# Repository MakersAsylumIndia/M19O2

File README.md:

# M19O2
DiY Oxygen Concentrator based on / inspired by the [OpenOx](https://github.com/hacklabkyiv/openox), [Marut](https://www.technido.com/marut), [RepRap](https://github.com/RepRapLtd/Oxygen-concentrator) and [Project Apollo](https://github.com/oxycon/ProjectApollo) platforms.

## About

Read about the project on [Hackaday](https://hackaday.com/2021/04/26/indian-makers-respond-to-the-covid-19-pandemic-by-producing-oxygen-concentrators/).
Also check out the project on the [hackaday.io](https://hackaday.io/project/181201-m19o2-oxygen-concentrator) project page.

The **M19O2** Oxygen Concentrator is "Open Source Hardware" as certified by the [OSHWA](https://certification.oshwa.org/in000029.html).
OSHWA UID for the M19O2 is **IN000029**

<a href="https://certification.oshwa.org/in000029.html">

## Contribute

You can contribute on the [Ketto fundraiser page](https://www.ketto.org/fundraiser/m19-oxygen-concentrators-make-in-india)

## Coordination lists

- [Notion workspace](https://www.notion.so/M-19-Collective-b44b9d8d7dd14d5d86d417facf0f4141) for the M19 collective.
- [M19O2 Master](https://docs.google.com/spreadsheets/d/1rJZ5P0rF2Or8yu0H8HEPz25RP8kTAXxbNVU87DqD-eM/edit#gid=0) sheet tracks the city-wise coordinators, tools, FAQs etc.
- [BOM M19O2](https://docs.google.com/spreadsheets/d/1gmmdXTP3EQk-4hCGVYj-FxzUMADlT8mw354VPmYt5A4/edit#gid=870920932) sheet lists the master Bill of Materials (BOM) along with city-wise BOM
- [Starting a community lab](https://docs.google.com/document/d/1oR9rhGmbcnoSBjzQCYwE9Anocvr0q5_VmuVkbnycx18/edit?usp=sharing) document and [Build List for Labs](https://docs.google.com/spreadsheets/d/1DynT9Mh8jcV9qHxwFuQxj1fcQQHj_v_ymwpoZD1L23g/edit?usp=sharing) sheet for lab onboarding information and coordination.

## Engineering

- [Labview testbench](engineering/software/M19-oxygen-concentrator-testbench) is a testbench executable developed by [Fracktal Works](https://github.com/FracktalWorks), useful for tuning the performance of your concentrator prototypes.
- [Computer-aided Design/Engineering](engineering/cad-cae) for design, version control and simulation data related to the M19O2 and its iterations. Committed to open-source and open-innovation.
- [Electronics](engineering/electronics) for all things electronics, including comprehensive design and development data of DIY [Oxygen Analyzers](engineering/electronics/oxygen_analysers) and other [subprojects](engineering/electronics/subprojects).

## How to use this repo

Open a terminal on your computer. Run

```bash
git clone https://github.com/MakersAsylumIndia/M19O2 && cd M19O2
git submodule update --init --recursive
```
The repository shall be available on your computer.
To periodically update the contents,

```bash
cd M19O2
git pull
git submodule update --init --recursive
```

## How to contribute to this repository

Fork this repository. You can find the command for this on the top-right of the webpage. This shall create a personal, updateable copy of this repository on your github account.

On your computer terminal, run

```bash
git clone https://github.com/<your-username>/M19O2 && cd M19O2
git submodule update --init --recursive
```
Add your contributions to this repository and save on github.

```bash
cd M19O2
git add .
git commit -m "<your-commit-message>"
git push origin
```

To contribute your work to the M19 Collective, open your repository in a browser and issue a pull request from your repository to the one at [Makers' Asylum](https://github.com/MakersAsylumIndia).

## License

Licenses

#### Hardware
CERN Open Hardware License Version 2 - Strongly Reciprocal ([CERN-OHL-S-2.0](https://spdx.org/licenses/CERN-OHL-S-2.0.html)).

#### Software
MIT open source [license](http://opensource.org/licenses/MIT).

#### Documentation:
<br />This work is licensed under a <a rel="license" href="http://creativecommons.org/licenses/by/4.0/">Creative Commons Attribution 4.0 International License</a>.

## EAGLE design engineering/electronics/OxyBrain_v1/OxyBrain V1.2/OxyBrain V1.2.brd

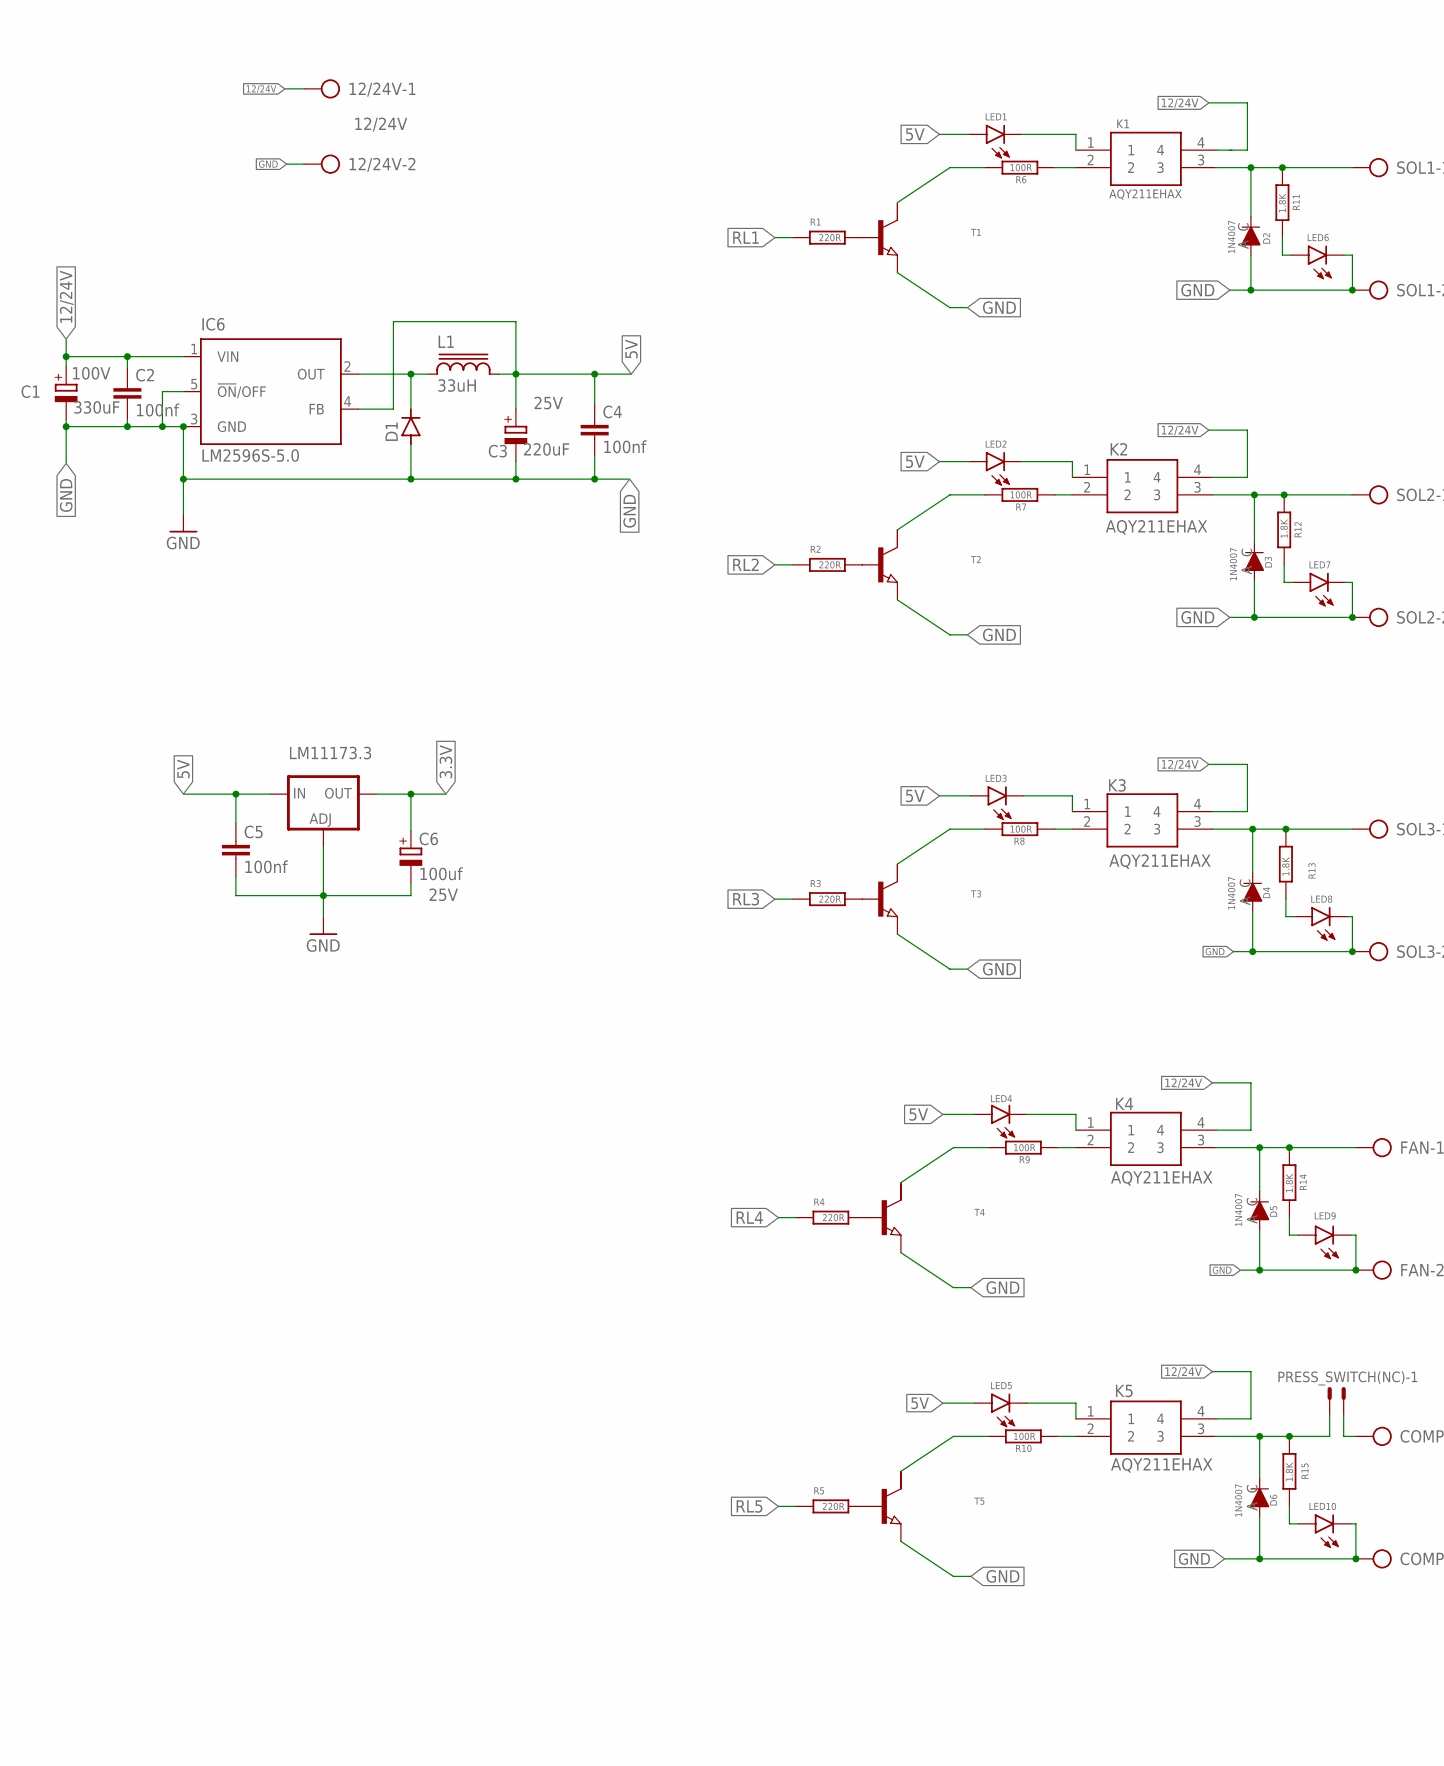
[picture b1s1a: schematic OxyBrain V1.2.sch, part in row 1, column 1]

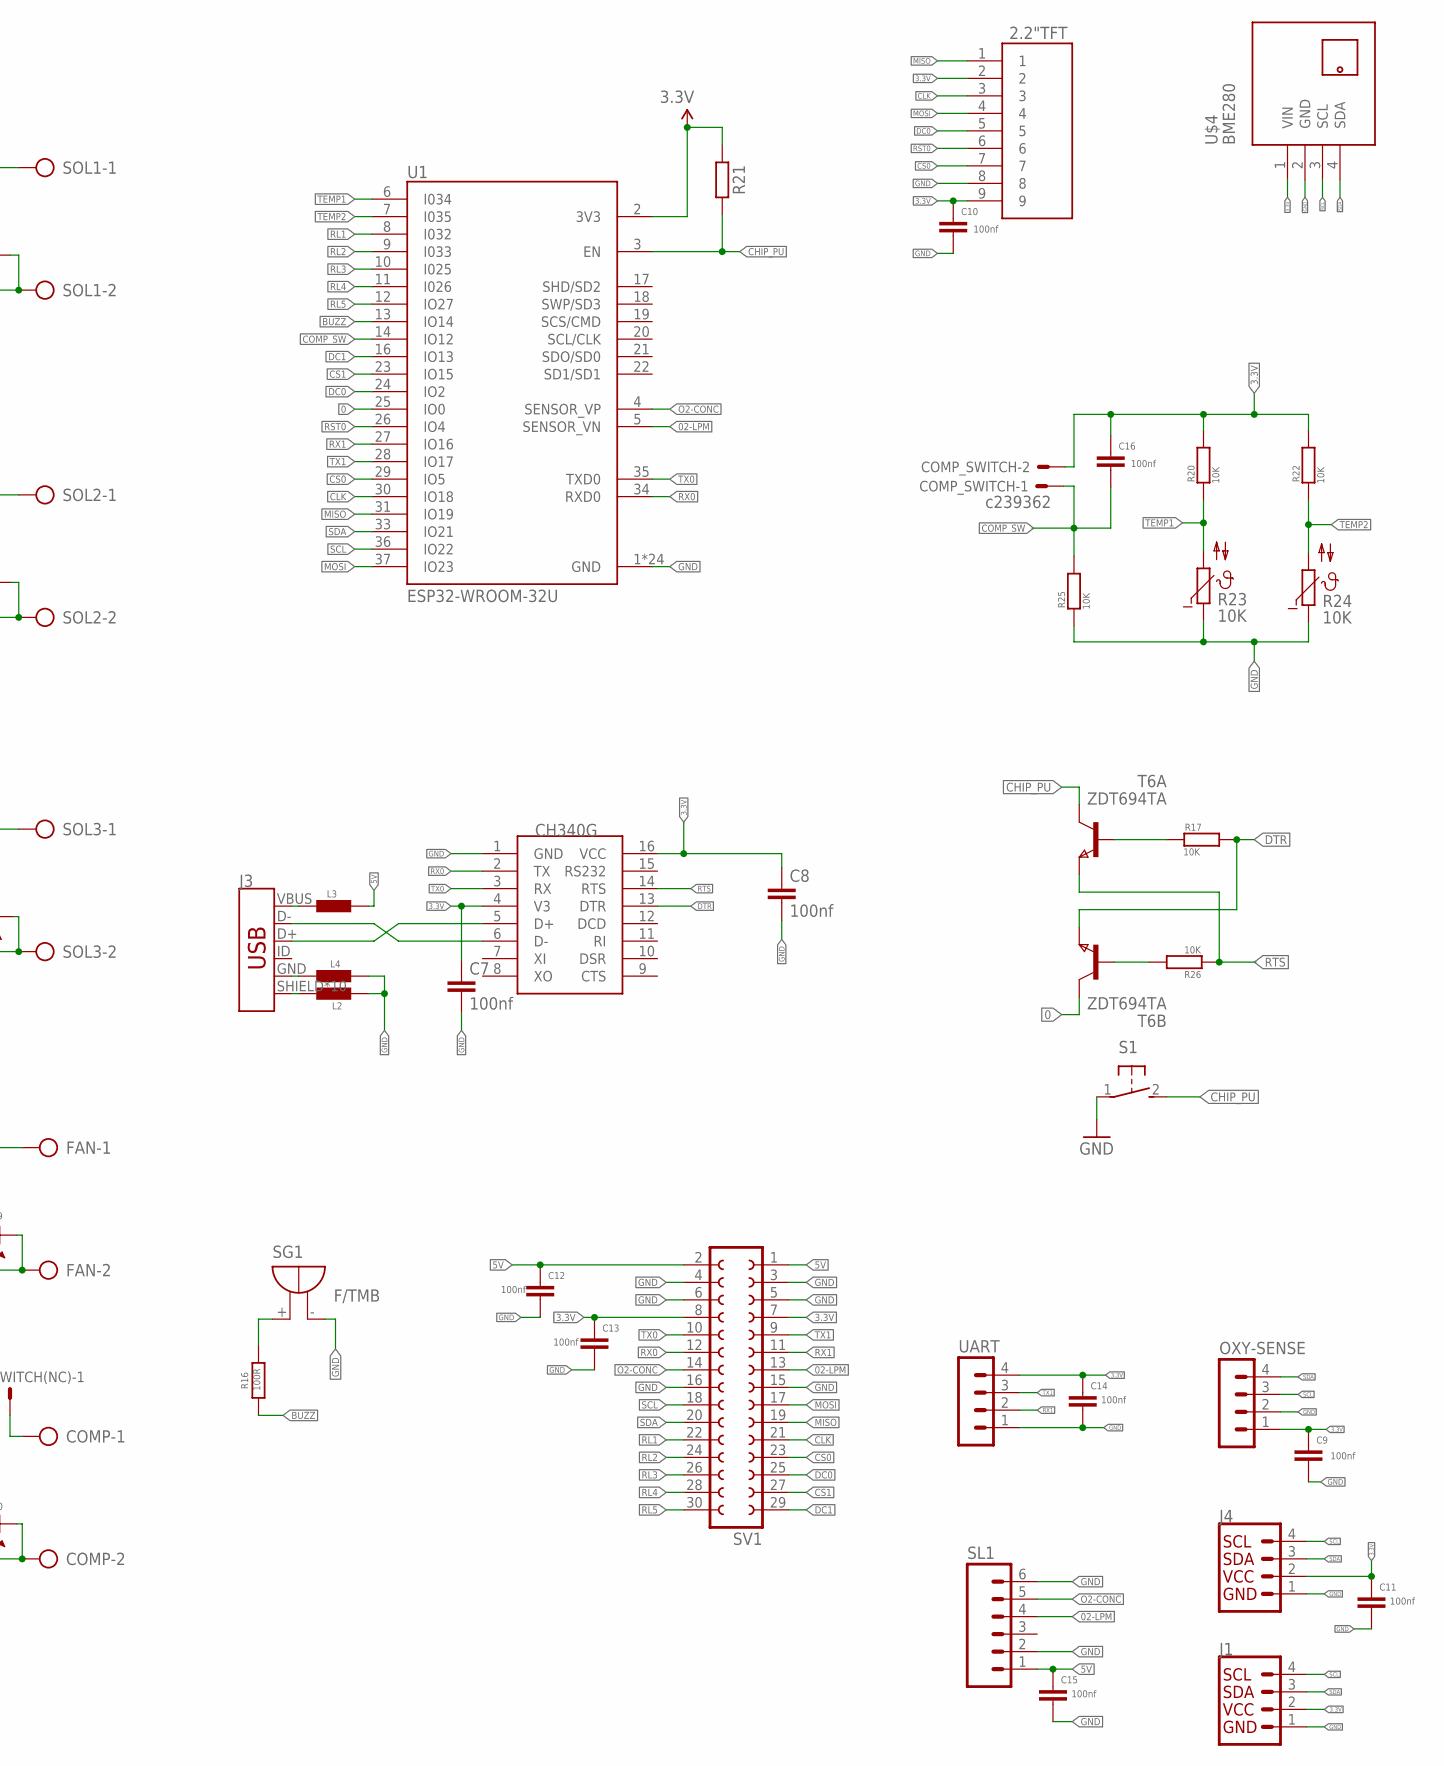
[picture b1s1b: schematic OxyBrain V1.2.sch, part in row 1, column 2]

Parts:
2.2"TFT: 1735446-9; SHDR9W60P0X200_1X9_2000X520X63
12/24V: 12/24V; AK500/2
C1: 330uF; 140CLH-1010; VOLTAGE 100V
C2, C4, C5, C7, C8, C9, C10, C11, C12, C13, C14, C15, C16: 100nf; C1206
C3: 220uF; 153CLV-0605; VOLTAGE 25V
C6: 100uf; 153CLV-0605; VOLTAGE 25V
COMP: AK500/2
COMP_SWITCH: c239362; 22-23-2021
D1: DIODE-SOD123; SOD123
D2, D3, D4, D5, D6: 1N4007; SOD-123FL
FAN: AK500/2
IC6: LM2596S-5.0; TO263-5
J1, J4: I2C_STANDARD; 1X04
J3: USB_MICRO-B_HALF_PTH_MILL; USB-MICROB-PTH-MILL
K1, K2, K3, K4, K5: AQY211EHAX; AQY21(SMD_DIP)
L1: 33uH; CDRH127/LD
L2, L3, L4: BLM15HD102SN1; 0402
LED1, LED2, LED3, LED4, LED5, LED6, LED7, LED8, LED9, LED10: LEDCHIPLED_1206; CHIPLED_1206
LM11173.3: LD117ADT33TR; DPACK
OXY-SENSE: MA04-1
PRESS_SWITCH(NC): c239362; 22-23-2021
R1, R2, R3, R4, R5: 220R; M1206
R6, R7, R8, R9, R10, R16: 100R; M1206
R11, R12, R13, R14, R15: 1.8K; M1206
R17, R20, R22, R25, R26: 10K; M1206
R21: 10k; M1206
R23, R24: 10K; P640
S1: B3U-1000P(M)-B; DTSM-3
SG1: F/TMB
SL1: M06; 06P
SOL1, SOL2, SOL3: AK500/2
SV1: FE15-2
T1, T2, T3, T4, T5: 600mA/40V; SOT89
T6: ZDT694TA; SM8
U1: ESP32-WROOM-32U; XCVR_ESP32-WROOM-32U
U$1: CH340G; SOIC16
U$4: BME280; TEMP-HUM-PRES-BME280
UART: MA04-1

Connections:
0: T6.7 (C), T6.8 (C), U1.25 (IO0)
02-LPM: SL1.4, SV1.13, U1.5 (SENSOR_VN)
3.3V: 2.2"TFT.2, 2.2"TFT.9, C6.+, C7.1, C8.1, C9.1, C10.1, C11.1, C13.1, C14.1, C16.1, COMP_SWITCH.2, J1.2, J4.2, LM11173.3.4 (OUT), OXY-SENSE.1, R20.1, R21.2, R22.1, SV1.7, SV1.8, U1.2 (3V3), U$1.4 (V3), U$1.16 (VCC), U$4.1 (VIN), UART.4
5V: C3.+, C4.1, C5.1, C12.1, C15.1, IC6.4 (FB), L1.2, L3.2, LED1.A, LED2.A, LED3.A, LED4.A, LED5.A, LM11173.3.3 (IN), SL1.1, SV1.1, SV1.2
12/24V: 12/24V.1, C1.+, C2.1, IC6.1 (VIN), K1.4, K2.4, K3.4, K4.4, K5.4
BUZZ: R16.1, U1.13 (IO14)
CHIP_PU: R21.1, S1.2, T6.5 (C), T6.6 (C), U1.3 (EN)
CLK: 2.2"TFT.3, SV1.21, U1.30 (IO18)
COMP1: COMP.1, PRESS_SWITCH(NC).2
COMP_ON1: D6.C (K), K5.3, PRESS_SWITCH(NC).1, R15.1
COMP_SW: C16.2, COMP_SWITCH.1, R25.1, U1.14 (IO12)
CS0: 2.2"TFT.7, SV1.23, U1.29 (IO5)
CS1: SV1.27, U1.23 (IO15)
DC0: 2.2"TFT.5, SV1.25, U1.24 (IO2)
DC1: SV1.29, U1.16 (IO13)
DTR: R17.1, T6.1 (E), U$1.13 (DTR)
GND: 2.2"TFT.8, 12/24V.2, C1.-, C2.2, C3.-, C4.2, C5.2, C6.-, C7.2, C8.2, C9.2, C10.2, C11.2, C12.2, C13.2, C14.2, C15.2, COMP.2, D1.A, D2.A, D3.A, D4.A, D5.A, D6.A, FAN.2, IC6.3 (GND), IC6.5 (!ON!/OFF), J1.1, J4.1, L2.2, L4.2, LED6.C, LED7.C, LED8.C, LED9.C, LED10.C, LM11173.3.1 (ADJ), OXY-SENSE.2, R23.1, R24.1, R25.2, S1.1, SG1.-, SL1.2, SL1.6, SOL1.2, SOL2.2, SOL3.2, SV1.3, SV1.4, SV1.5, SV1.6, SV1.15, SV1.16, T1.3 (E), T2.3 (E), T3.3 (E), T4.3 (E), T5.3 (E), U1.1 (GND), U1.15 (GND), U1.38 (GND), U1.G.1 (GND), U1.G.2 (GND), U1.G.4 (GND), U1.G.5 (GND), U1.G.6 (GND), U1.G.7 (GND), U1.G.8 (GND), U1.G.9 (GND), U1.G.10 (GND), U1.G.11 (GND), U1.G.12 (GND), U1.G.13 (GND), U1.G.14 (GND), U1.G.15 (GND), U1.G.16 (GND), U1.G.17 (GND), U1.G.18 (GND), U1.G.19 (GND), U1.G.20 (GND), U1.G.21 (GND), U1.G.22 (GND), U$1.1 (GND), U$4.2 (GND), UART.1
MISO: 2.2"TFT.1, SV1.19, U1.31 (IO19)
MOSI: 2.2"TFT.4, SV1.17, U1.37 (IO23)
unnamed: K1.2, R6.1
unnamed: K2.2, R7.1
unnamed: D3.C (K), K2.3, R12.1, SOL2.1
unnamed: K2.1, LED2.C
unnamed: K1.1, LED1.C
unnamed: R2.2, T2.1 (B)
unnamed: R7.2, T2.2 (C)
unnamed: K3.1, LED3.C
unnamed: D2.C (K), K1.3, R11.1, SOL1.1
unnamed: K4.1, LED4.C
unnamed: LED7.A, R12.2
unnamed: K3.2, R8.1
unnamed: R1.2, T1.1 (B)
unnamed: D4.C (K), K3.3, R13.1, SOL3.1
unnamed: R3.2, T3.1 (B)
unnamed: R8.2, T3.2 (C)
unnamed: R6.2, T1.2 (C)
unnamed: J3.VBUS, L3.1
unnamed: R16.2, SG1.+
unnamed: R5.2, T5.1 (B)
unnamed: R10.2, T5.2 (C)
unnamed: R17.2, T6.4 (B)
unnamed: R26.1, T6.2 (B)
unnamed: K4.2, R9.1
unnamed: LED10.A, R15.2
unnamed: LED6.A, R11.2
unnamed: K5.1, LED5.C
unnamed: LED8.A, R13.2
unnamed: K5.2, R10.1
unnamed: D5.C (K), FAN.1, K4.3, R14.1
unnamed: R4.2, T4.1 (B)
unnamed: R9.2, T4.2 (C)
unnamed: J3.GND, L4.1
unnamed: LED9.A, R14.2
unnamed: J3.SHIELD, J3.SHIELD2 (SHIELD), J3.SHIELD3 (SHIELD), J3.SHIELD4 (SHIELD), J3.SHIELD5 (SHIELD), J3.SHIELD6 (SHIELD), J3.SHIELD7 (SHIELD), J3.SHIELD8 (SHIELD), J3.SHIELD9 (SHIELD), J3.SHIELD10 (SHIELD), L2.1
unnamed: J3.D-, U$1.6 (D-)
unnamed: J3.D+, U$1.5 (D+)
O2-CONC: SL1.5, SV1.14, U1.4 (SENSOR_VP)
OUT: D1.C, IC6.2 (OUT), L1.1
RL1: R1.1, SV1.22, U1.8 (I032)
RL2: R2.1, SV1.24, U1.9 (I033)
RL3: R3.1, SV1.26, U1.10 (I025)
RL4: R4.1, SV1.28, U1.11 (I026)
RL5: R5.1, SV1.30, U1.12 (IO27)
RST0: 2.2"TFT.6, U1.26 (IO4)
RTS: R26.2, T6.3 (E), U$1.14 (RTS)
RX0: SV1.12, U1.34 (RXD0), U$1.2 (TX)
RX1: SV1.11, U1.27 (IO16), UART.2
SCL: J1.4, J4.4, OXY-SENSE.3, SV1.18, U1.36 (IO22), U$4.3 (SCL)
SDA: J1.3, J4.3, OXY-SENSE.4, SV1.20, U1.33 (IO21), U$4.4 (SDA)
TEMP1: R20.2, R23.2, U1.6 (I034)
TEMP2: R22.2, R24.2, U1.7 (I035)
TX0: SV1.10, U1.35 (TXD0), U$1.3 (RX)
TX1: SV1.9, U1.28 (IO17), UART.3

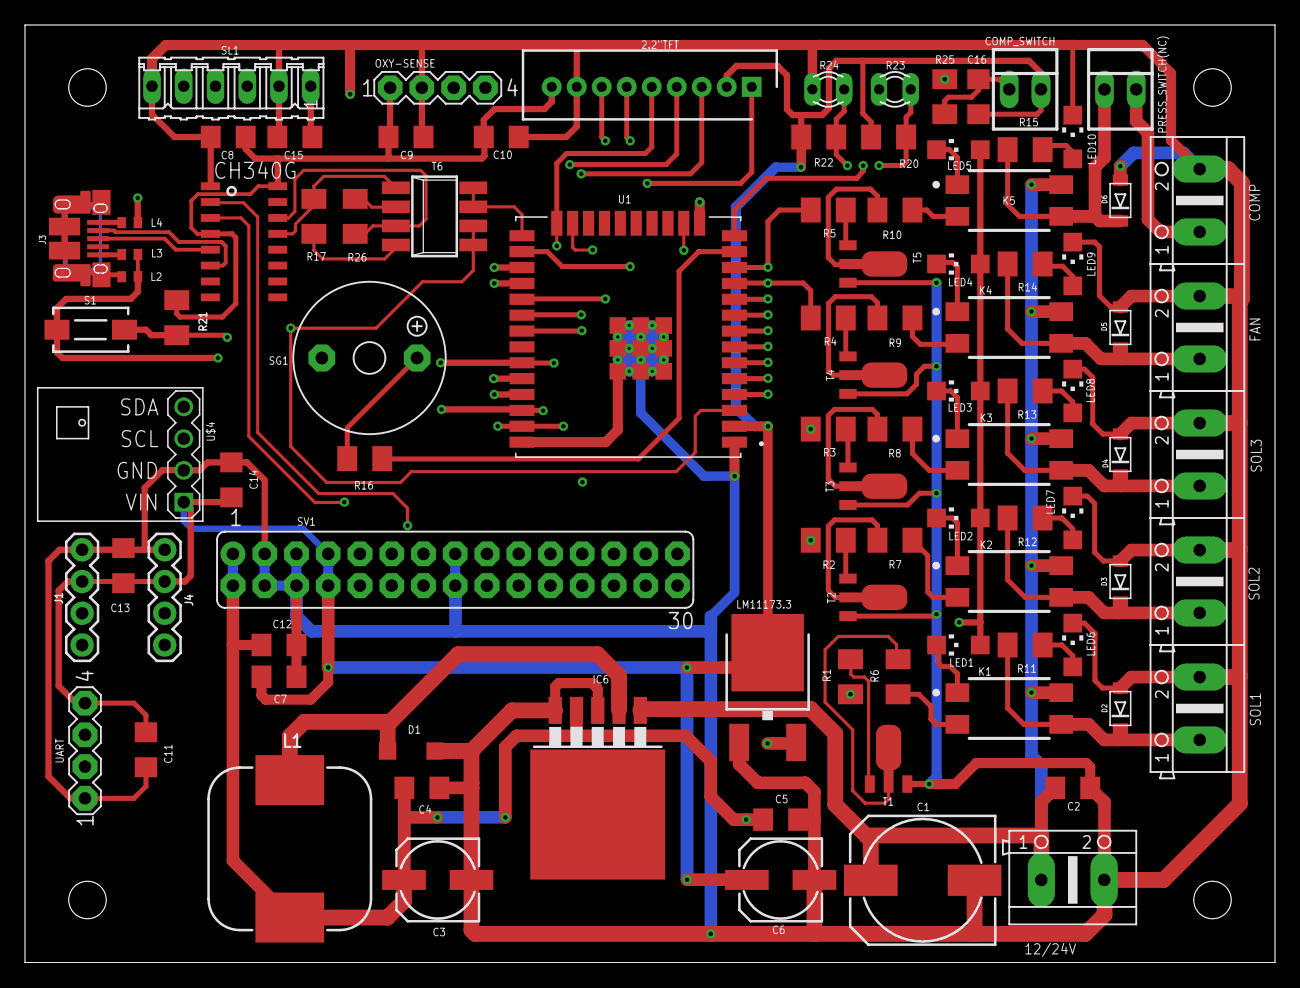
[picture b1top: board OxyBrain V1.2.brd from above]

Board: 4 copper layers, 100.0 x 75.0 mm, 94 parts (0 on the bottom side), 73 nets.

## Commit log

2021-04-28 initial commit for M19 OxiKit project
2021-04-28 Update README.md
    added render image
2021-04-29 electronics sub-project
2021-04-29 DOC: project coordination links
2021-04-29 renamed images
2021-04-30 Added README and starting CAD content
2021-04-30 [FEATURE] Submodules for cad and sd - argo-1 repos at the moment
2021-04-30 Updated submodules
2021-04-30 Oxikit DIY oxygen analyser documents added.
2021-04-30 updated SD
2021-04-30 basic update
2021-04-30 added empty CAE submodule
2021-04-30 CAE submodule added and set-up
2021-04-30 simple fix
2021-04-30 Added submodule for electronics
2021-04-30 Added instructables.com page (.html)
2021-04-30 updated electronics submodule
2021-04-30 OxiKit docs
2021-05-01 Added valve step files to cad submodule
2021-05-01 Completed all individual parts' step-file conversion
2021-05-01 Updated CAD submodule
2021-05-01 Started FreeCAD Assembly of OxiKit v22
2021-05-01 Made frame FreeCAD assembly. Unconstrained. Added to parent assembly
2021-05-01 Updated CAD assembly of v22
2021-05-02 Updated tubing on freecad assembly
2021-05-02 Updated assembly - top solenoid fitting - reset tubes
2021-05-02 Updated tanks in assembly
2021-05-02 Updated assembly (unconstrained). Only tubing left.
2021-05-03 Merged and updated electronics folder.
2021-05-06 [FEATURE] Merged MeshAssembly PR
2021-05-07 ENH: add a period
2021-05-07 DOC: minor phrase update
2021-05-19 Simplified structure. Removed submodules, for now.
2021-05-19 [FEATURE] Restructuring.
2021-05-19 Wiki markdown copies added to /docs. THESE FILES ARE NOT LINKED TO THE WIKI TAB DIRECTLY
2021-05-21 Simulation research and IISc docs
2021-05-21 tata doc
2021-05-21 Added lab onboarding to README.md
2021-05-21 nafion tubes paper
2021-05-22 [FEATURE]Added Labview testbench. Updated README.md
2021-05-22 [FIX] Readme typo
2021-05-22 [ENHANCEMENT] Updated README.md
2021-05-23 [FEATURE] DIY Oxygen Analyzer
2021-05-23 [FIX] rearrange
2021-05-24 [FIX] Readme link
2021-05-24 [FEATURE] Add Karan's project. Minor restructuring
2021-05-25 [ENHANCEMENT] expanded deployment folder structure
2021-06-01 Brainboard by @shridattdudhat added
2021-06-01 Fracktal firmware
2021-06-10 [FEATURE] Add Fracktal Works OC data
2021-06-10 added humidity alarm
2021-06-10 Update README.md
    Edited readme
2021-06-10 added O2 sensor adapter
2021-06-11 Updated Readme - notion
2021-06-11 update readme - notion
2021-06-11 [fix] prune stale submodule
2021-06-12 added LiX zeolite timing code WIP
2021-06-14 added Sieve aluminum extrusion assembly in CAD folder WIP
2021-06-18 sieve bed exploded view, patent and extrustion standard
2021-06-18 sieve bed exploded view, patent and extrustion standard (#21)
2021-06-27 Update README.md
    minor updates
2021-06-27 Sieve Assembly, Sieve Compression Jig, Humidity Sensor housings etc
2021-06-27 added logos
2021-06-29 folder restructuring and added M19O2 wiring in Electronics
2021-06-30 started M19O2_v4 CAD assy
2021-07-04 finished M19O2_v4 CAD assy
2021-07-05 M19O2 pneumatic circuit added
2021-07-08 [FEATURE] WHO guidelines
2021-07-09 M19O2 CAD updates
2021-07-16 M19O2 pneumatic wiring update
2021-07-17 M19O2 added O2 sensor measurement code and main code
2021-07-26 M19O2 Datasheet & Instruction Manual update
2021-07-30 M19O2 Oxygen sensor mount
    M19O2 Oxygen sensor mount
2021-08-06 M19O2 extracted assembly images from CAD
2021-08-06 M19O2 added better renders for readme.md
2021-08-13 M19O2 several incremental updates
2021-08-13 M19O2 assembly manual added
2021-08-13 Update README.md
    added hackaday.io project page link
2021-08-19 M19O2 added moisture separator and auto drain STEP files
2021-08-24 added OSHWA certification logo
2021-09-04 big push - added Hour Counter, and modified all renders and drawings
2021-09-17 some updates
2021-09-17 documents update
2021-10-21 documentation updates
2022-11-21 added hi-res 3D CAD renders

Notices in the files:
README.md:
Open Source Licenses Facts
parts and their libraries:
SparkFun-Connectors: Licensing: Creative Commons ShareAlike 4.0 International - https://creativecommons.org/licenses/by-sa/4.0
inductor-sumida: Copyright (C) 2008, Bob Starr
SparkFun: Licensing: CC v3.0 Share-Alike You are welcome to use this library for commercial purposes.
